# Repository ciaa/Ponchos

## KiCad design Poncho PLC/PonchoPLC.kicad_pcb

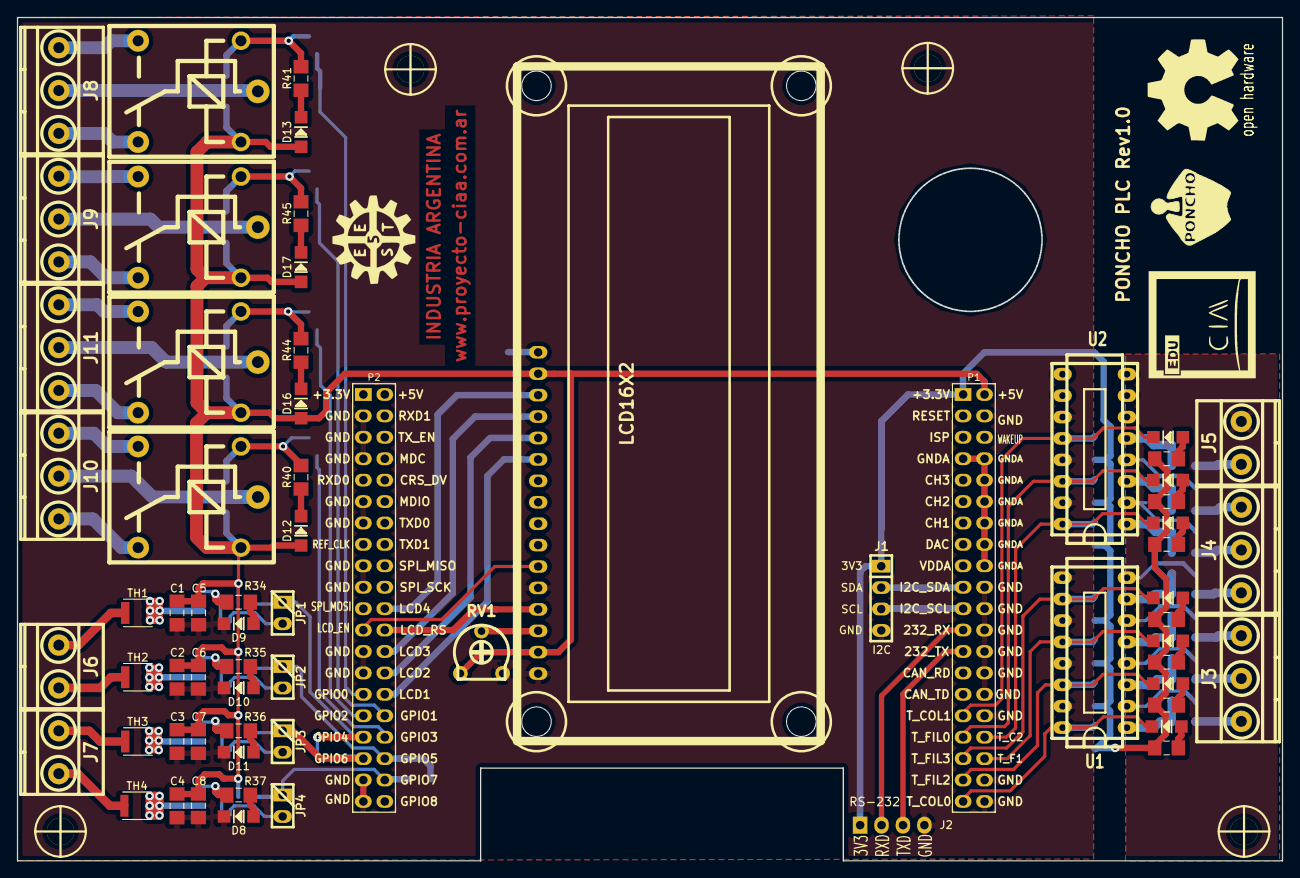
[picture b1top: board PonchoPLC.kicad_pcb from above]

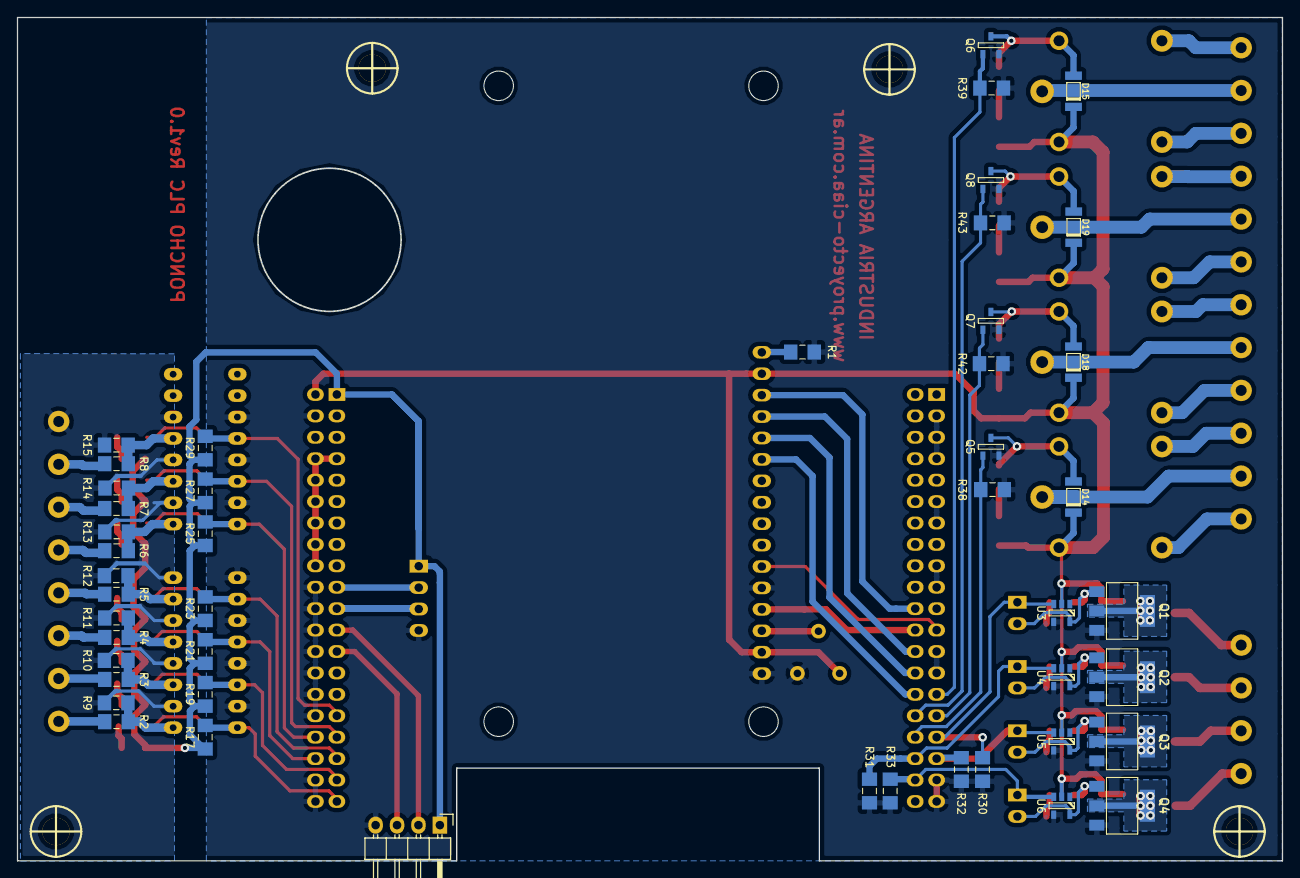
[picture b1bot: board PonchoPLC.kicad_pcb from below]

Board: 2 copper layers, 150.0 x 100.0 mm, 118 parts (47 on the bottom side), 89 nets.

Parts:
C1, C2, C3, C4: 100nF; C_1206
C5, C6, C7, C8: 1uF; C_1206
D1, D2, D3, D4, D5, D6, D7, D8, D9, D10, D11, D12, D13, D16, D17: LED red; LED_1206
D14, D15, D18, D19: LL4148; SOD80C
DS1: LCD16X2; LCD_16x2
G1: LOGO; LOGO_EESTN5
G2: LOGO; Logo_silk_OSHW_12x13mm
H1, H2, H3, H4: Mounting_Hole; Separador_M3_5mm
J1: I2C; pin_strip_4
J2: RS-232; HEADER-4H
J3, J4, J8, J9, J10, J11: TB_1X3; BORNERA3
J5, J6, J7: TB_1X2; BORNERA2
JP1, JP2, JP3, JP4: Jumper; Pin_strip_2
K1, K2, K3, K4: RELAY_C; Relay_C
Q1, Q2, Q3, Q4: FQT13N06L; SOT-223
Q5, Q6, Q7, Q8: 2N7002; SOT23
R1: 100; R_1206
R2, R3, R4, R5, R6, R7, R8: 3.3k; R_1206
R9, R10, R11, R12, R13, R14, R15: 4.7k; R_1206
R16, R18, R20, R22, R24, R26, R28: 2.2k; R_1206
R17, R19, R21, R23, R25, R27, R29, R30, R31, R32, R33, R38, R39, R42, R43: 100k; R_1206
R34, R35, R36, R37, R40, R41, R44, R45: 330; R_1206
RV1: 10K; TRIMER_V
TH1, TH2, TH3, TH4: PTS12066V100; PTC_1210
U1, U2: TLP627-4; DIP_16-300_socket
U3, U4, U5, U6: MCP1416; SOT-23-5
XA1: Conn_Poncho2P_2x_20x2; Conector_EDU_CIA_SOLO

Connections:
+3V3: J1.1, J2.1, R16.2, R17.2, R18.2, R19.2, R20.2, R21.2, R22.2, R23.2, R24.2, R25.2, R26.2, R27.2, R28.2, R29.2, XA1.1
+5V: C1.2, C2.2, C3.2, C4.2, C5.2, C6.2, C7.2, C8.2, D12.1, D13.1, D14.2, D15.2, D16.1, D17.1, D18.2, D19.2, DS1.2, DS1.15, K1.5, K2.5, K3.5, K4.5, RV1.1, U3.2, U4.2, U5.2, U6.2, XA1.2
/Conector del Poncho/COL1: D7.2, R29.1, U2.12, XA1.31
/Conector del Poncho/COL2: D5.2, R25.1, U2.16, XA1.34
/Conector del Poncho/LCD1: DS1.11, XA1.70
/Conector del Poncho/LCD2: DS1.12, XA1.68
/Conector del Poncho/LCD3: DS1.13, XA1.66
/Conector del Poncho/LCD4: DS1.14, XA1.62
/Conector del Poncho/LCD_EN: DS1.6, XA1.63
/Conector del Poncho/RS: DS1.4, XA1.64
/Conector del Poncho/RXD: J2.2, XA1.23
/Conector del Poncho/SCL: J1.3, XA1.21
/Conector del Poncho/SDA: J1.2, XA1.19
/Conector del Poncho/TXD: J2.3, XA1.25
/DIN4: D1.2, R17.1, U1.16, XA1.39
/Entradas Optoacopladas/DIN2: D6.2, R27.1, U2.14, XA1.33
/Entradas Optoacopladas/DIN3: D3.2, R21.1, U1.12, XA1.36
/Entradas Optoacopladas/DIN5: D2.2, R19.1, U1.14, XA1.37
/Entradas Optoacopladas/DIN6: D4.2, R23.1, U1.10, XA1.35
/Entradas Optoacopladas/IN0: J3.1, R2.1
/Entradas Optoacopladas/IN1: J3.2, R3.1
/Entradas Optoacopladas/IN2: J3.3, R4.1
/Entradas Optoacopladas/IN3: J4.1, R5.1
/Entradas Optoacopladas/IN4: J4.2, R6.1
/Entradas Optoacopladas/IN5: J4.3, R7.1
/Entradas Optoacopladas/IN6: J5.1, R8.1
/Salidas Digitales/C1A: J8.2, K2.1
/Salidas Digitales/C1B: J9.2, K4.1
/Salidas Digitales/C1C: J10.2, K1.1
/Salidas Digitales/C1D: J11.2, K3.1
/Salidas Digitales/DOUT0: Q6.1, R39.1, XA1.69
/Salidas Digitales/DOUT1: Q8.1, R43.1, XA1.72
/Salidas Digitales/DOUT2: Q7.1, R42.1, XA1.71
/Salidas Digitales/DOUT3: Q5.1, R38.1, XA1.74
/Salidas Digitales/DOUT4: JP1.1, R30.1, U3.3, XA1.73
/Salidas Digitales/DOUT5: JP2.1, R31.1, U4.3, XA1.76
/Salidas Digitales/DOUT6: JP3.1, R32.1, U5.3, XA1.75
/Salidas Digitales/DOUT7: JP4.1, R33.1, U6.3, XA1.78
/Salidas Digitales/NC1A: J8.3, K2.4
/Salidas Digitales/NC1B: J9.3, K4.4
/Salidas Digitales/NC1C: J10.3, K1.4
/Salidas Digitales/NC1D: J11.3, K3.4
/Salidas Digitales/NO1A: J8.1, K2.3
/Salidas Digitales/NO1B: J9.1, K4.3
/Salidas Digitales/NO1C: J10.1, K1.3
/Salidas Digitales/NO1D: J11.1, K3.3
GND: C1.1, C2.1, C3.1, C4.1, C5.1, C6.1, C7.1, C8.1, D8.2, D9.2, D10.2, D11.2, DS1.1, DS1.5, J1.4, J2.4, Q1.3, Q2.3, Q3.3, Q4.3, Q5.3, Q6.3, Q7.3, Q8.3, R1.2, R30.2, R31.2, R32.2, R33.2, R38.2, R39.2, R42.2, R43.2, RV1.3, U1.9, U1.11, U1.13, U1.15, U2.11, U2.13, U2.15, U3.4, U4.4, U5.4, U6.4, XA1.4, XA1.20, XA1.22, XA1.24, XA1.26, XA1.28, XA1.30, XA1.32, XA1.38, XA1.40, XA1.43, XA1.45, XA1.47, XA1.51, XA1.53, XA1.57, XA1.59, XA1.65, XA1.67, XA1.77, XA1.79
GNDA: XA1.7, XA1.8, XA1.10, XA1.12, XA1.14, XA1.16, XA1.18
GNDD: J5.2, R9.1, R10.1, R11.1, R12.1, R13.1, R14.1, R15.1, U1.2, U1.4, U1.6, U1.8, U2.2, U2.4, U2.6
unnamed: D1.1, R16.1
unnamed: D2.1, R18.1
unnamed: D3.1, R20.1
unnamed: D4.1, R22.1
unnamed: D5.1, R24.1
unnamed: D6.1, R26.1
unnamed: D7.1, R28.1
unnamed: D8.1, R37.1
unnamed: D9.1, R34.1
unnamed: D10.1, R35.1
unnamed: D11.1, R36.1
unnamed: D12.2, R40.2
unnamed: D13.2, R41.2
unnamed: D14.1, K1.2, Q5.2, R40.1
unnamed: D15.1, K2.2, Q6.2, R41.1
unnamed: D16.2, R44.2
unnamed: D17.2, R45.2
unnamed: D18.1, K3.2, Q7.2, R44.1
unnamed: D19.1, K4.2, Q8.2, R45.1
unnamed: DS1.3, RV1.2
unnamed: DS1.16, R1.1
unnamed: J6.1, TH1.2
unnamed: J6.2, TH2.2
unnamed: J7.1, TH3.2
unnamed: J7.2, TH4.2
unnamed: JP1.2, Q1.1, R34.2, U3.5
unnamed: JP2.2, Q2.1, R35.2, U4.5
unnamed: JP3.2, Q3.1, R36.2, U5.5
unnamed: JP4.2, Q4.1, R37.2, U6.5
unnamed: Q1.2, Q1.4, TH1.1
unnamed: Q2.2, Q2.4, TH2.1
unnamed: Q3.2, Q3.4, TH3.1
unnamed: Q4.2, Q4.4, TH4.1
unnamed: R2.2, R9.2, U1.1
unnamed: R3.2, R10.2, U1.3
unnamed: R4.2, R11.2, U1.5
unnamed: R5.2, R12.2, U1.7
unnamed: R6.2, R13.2, U2.1
unnamed: R7.2, R14.2, U2.3
unnamed: R8.2, R15.2, U2.5

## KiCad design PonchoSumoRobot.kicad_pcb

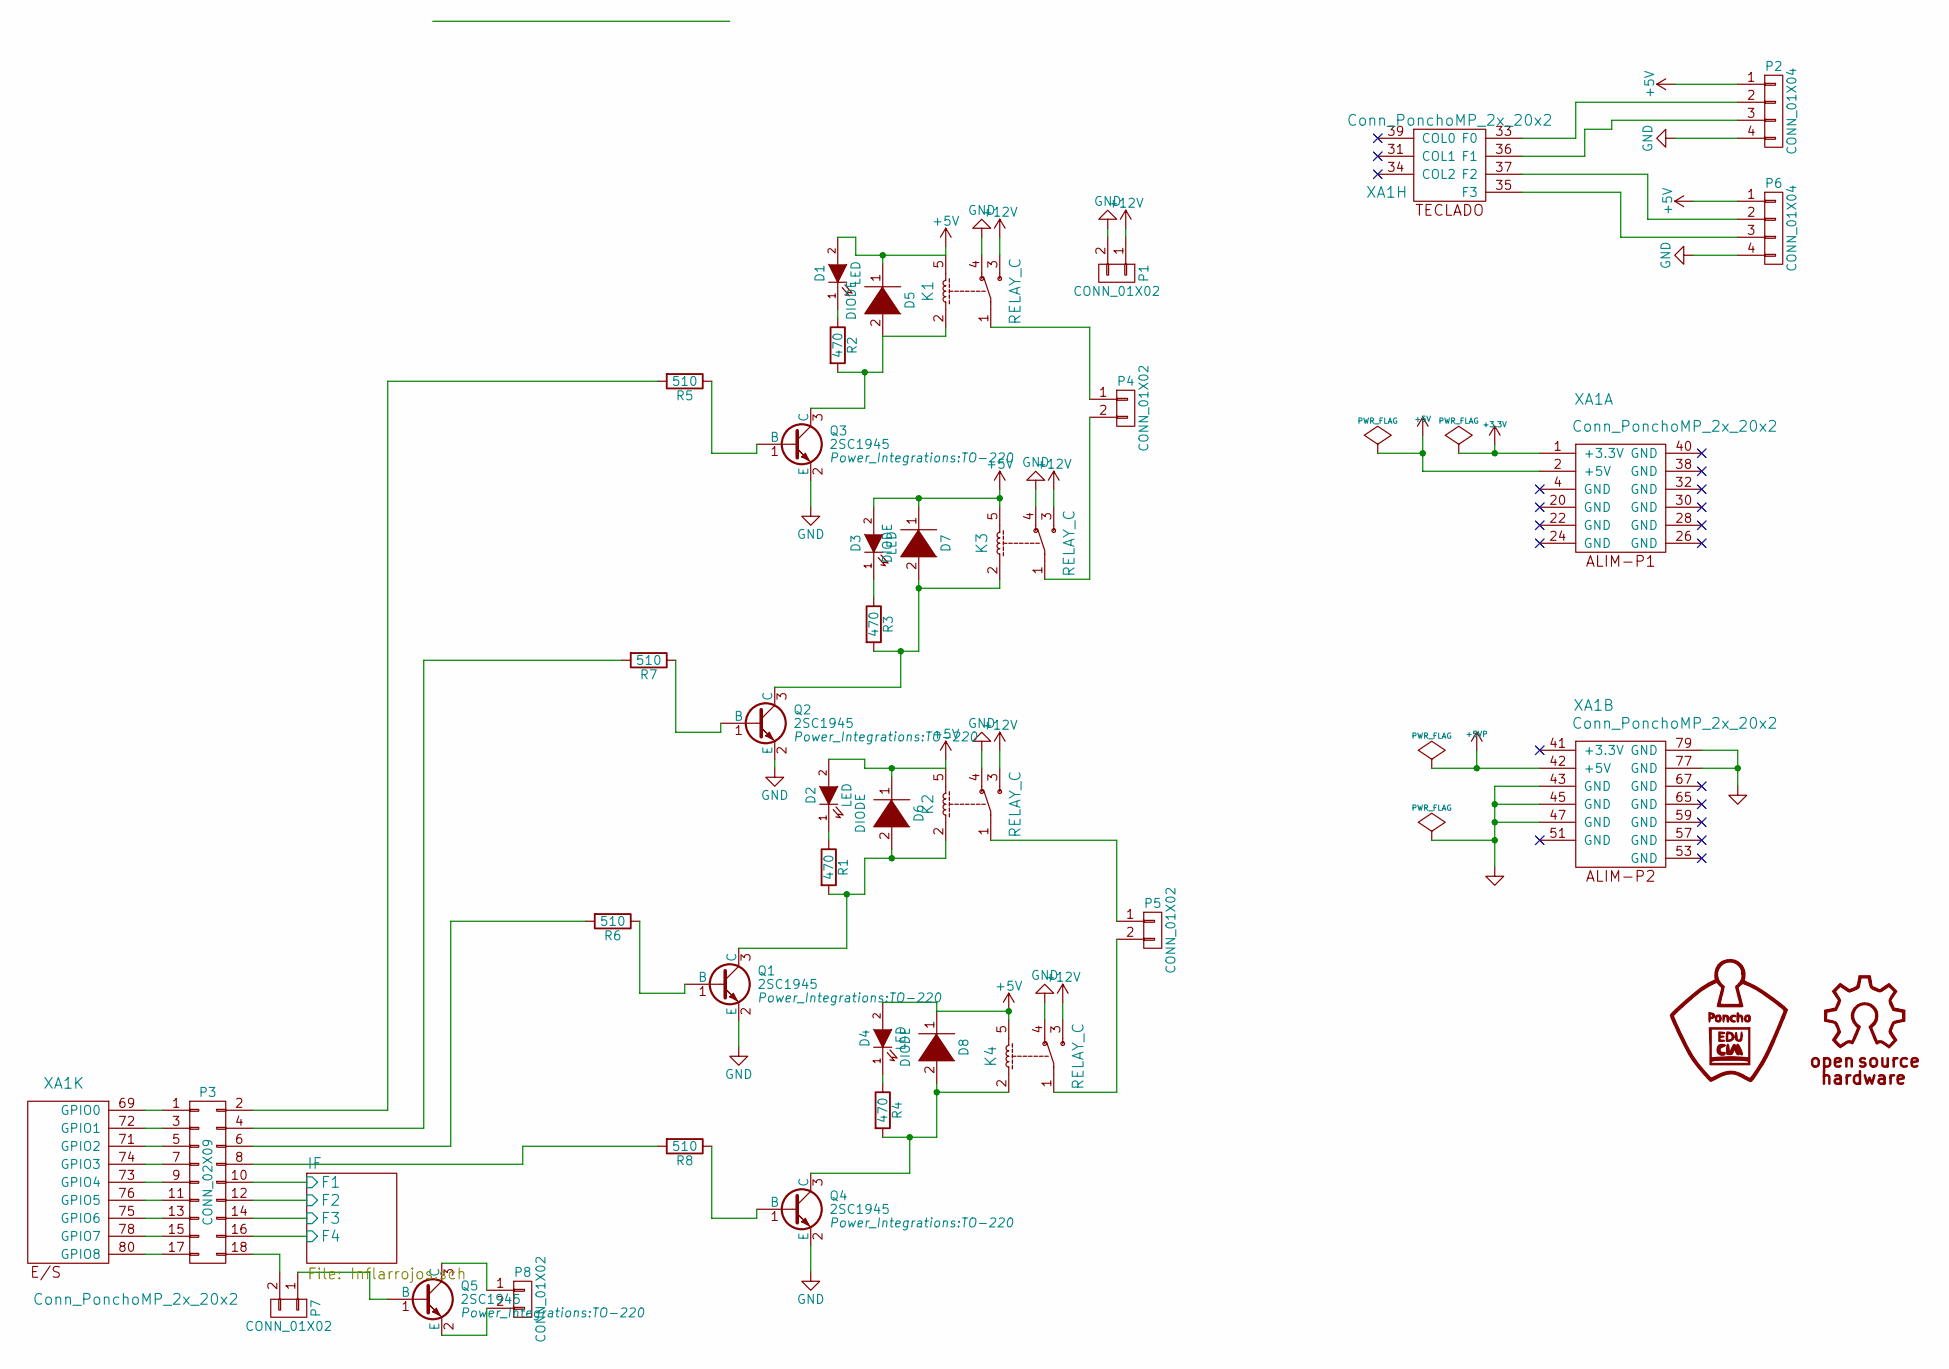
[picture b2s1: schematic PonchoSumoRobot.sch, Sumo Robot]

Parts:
D1, D2, D3, D4: LED; LED-3MM
D5, D6, D7, D8: DIODE; Diode_DO-41_SOD81_Horizontal_RM10
K1, K2, K3, K4: RELAY_C; Relay_SANYOU_SRD_Series_Form_C
P1, P4, P5: CONN_01X02; bornier2
P2, P6: CONN_01X04; Pin_Header_Straight_1x04
P3: CONN_02X09; Pin_Header_Straight_2x09
P7, P8: CONN_01X02; Pin_Header_Straight_1x02
Q1, Q2, Q3, Q4, Q5: 2SC1945; TO-220
R1, R2, R3, R4: 470; Resistor_Horizontal_RM7mm
R5, R6, R7, R8: 510; Resistor_Horizontal_RM7mm
XA1: Conn_PonchoMP_2x_20x2; Conn_Poncho_SinBorde

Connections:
+3V3: XA1.1 (+3.3V)
+5VP: XA1.42 (+5V)
+12V: K1.3, K2.3, K3.3, K4.3, P1.1
/IF/F1: P3.10; also elsewhere on the board
/IF/F2: P3.12; also elsewhere on the board
/IF/F3: P3.14; also elsewhere on the board
/IF/F4: P3.16; also elsewhere on the board
GND: K1.4, K2.4, K3.4, K4.4, P1.2, P2.4, P6.4, Q1.2 (E), Q2.2 (E), Q3.2 (E), Q4.2 (E), XA1.43 (GND), XA1.45 (GND), XA1.47 (GND), XA1.77 (GND), XA1.79 (GND); also elsewhere on the board
unnamed: D1.1 (K), R2.1
unnamed: D2.1 (K), R1.1
unnamed: D3.1 (K), R3.1
unnamed: D4.1 (K), R4.1
unnamed: D5.2 (A), K1.2, Q3.3 (C), R2.2
unnamed: D6.2 (A), K2.2, Q1.3 (C), R1.2
unnamed: D7.2 (A), K3.2, Q2.3 (C), R3.2
unnamed: D8.2 (A), K4.2, Q4.3 (C), R4.2
unnamed: K1.1, P4.1
unnamed: K2.1, P5.1
unnamed: K3.1, P4.2
unnamed: K4.1, P5.2
unnamed: P2.2, XA1.33 (F0)
unnamed: P2.3, XA1.36 (F1)
unnamed: P3.1, XA1.69 (GPIO0)
unnamed: P3.2, R5.2
unnamed: P3.3, XA1.72 (GPIO1)
unnamed: P3.4, R7.2
unnamed: P3.5, XA1.71 (GPIO2)
unnamed: P3.6, R6.2
unnamed: P3.7, XA1.74 (GPIO3)
unnamed: P3.8, R8.2
unnamed: P3.9, XA1.73 (GPIO4)
unnamed: P3.11, XA1.76 (GPIO5)
unnamed: P3.13, XA1.75 (GPIO6)
unnamed: P3.15, XA1.78 (GPIO7)
unnamed: P3.17, XA1.80 (GPIO8)
unnamed: P3.18, P7.2
unnamed: P6.2, XA1.37 (F2)
unnamed: P6.3, XA1.35 (F3)
unnamed: P7.1, Q5.1 (B)
unnamed: Q1.1 (B), R6.1
unnamed: Q2.1 (B), R7.1
unnamed: Q3.1 (B), R5.1
unnamed: Q4.1 (B), R8.1

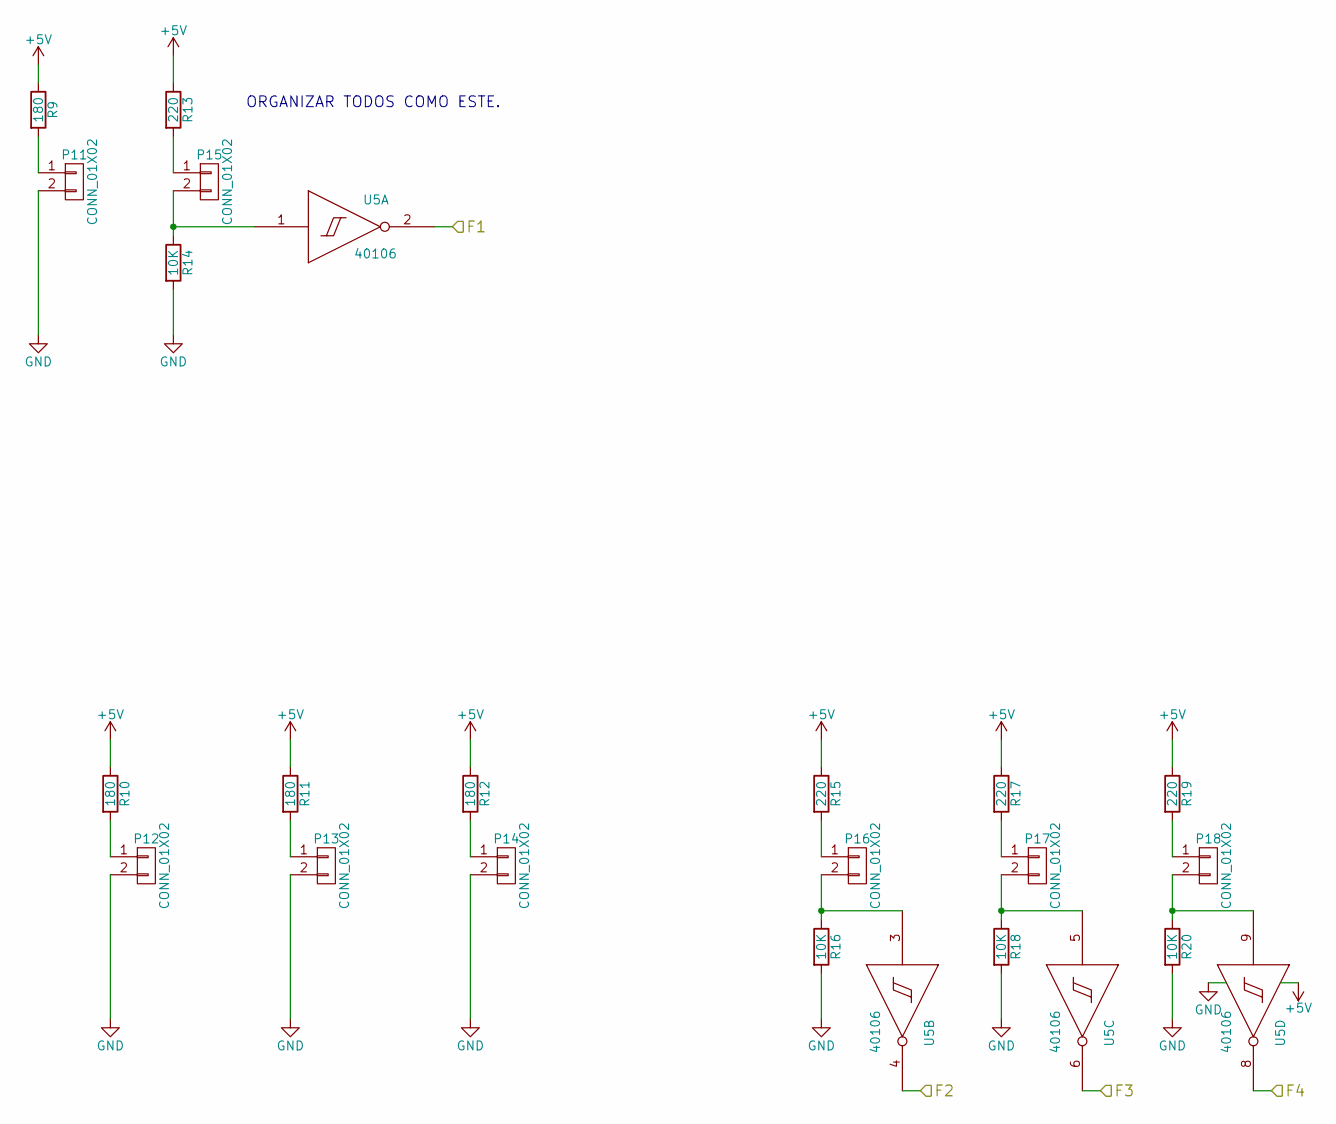
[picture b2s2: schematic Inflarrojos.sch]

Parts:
P11, P12, P13, P14, P15, P16, P17, P18: CONN_01X02; Pin_Header_Straight_1x02
R9, R10, R11, R12: 180; Resistor_Horizontal_RM7mm
R13, R15, R17, R19: 220; Resistor_Horizontal_RM7mm
R14, R16, R18, R20: 10K; Resistor_Horizontal_RM7mm
U5: 40106; 40xx-DIL14

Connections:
/IF/F1: U5.2 (Out); also elsewhere on the board
/IF/F2: U5.4 (Out); also elsewhere on the board
/IF/F3: U5.6 (Out); also elsewhere on the board
/IF/F4: U5.8 (Out); also elsewhere on the board
GND: P11.2, P12.2, P13.2, P14.2, R14.2, R16.2, R18.2, R20.2, U5.7 (VSS); also elsewhere on the board
unnamed: P11.1, R9.2
unnamed: P12.1, R10.2
unnamed: P13.1, R11.2
unnamed: P14.1, R12.2
unnamed: P15.1, R13.2
unnamed: P15.2, R14.1, U5.1 (In)
unnamed: P16.1, R15.2
unnamed: P16.2, R16.1, U5.3 (In)
unnamed: P17.1, R17.2
unnamed: P17.2, R18.1, U5.5 (In)
unnamed: P18.1, R19.2
unnamed: P18.2, R20.1, U5.9 (In)

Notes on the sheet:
ORGANIZAR TODOS COMO ESTE.

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
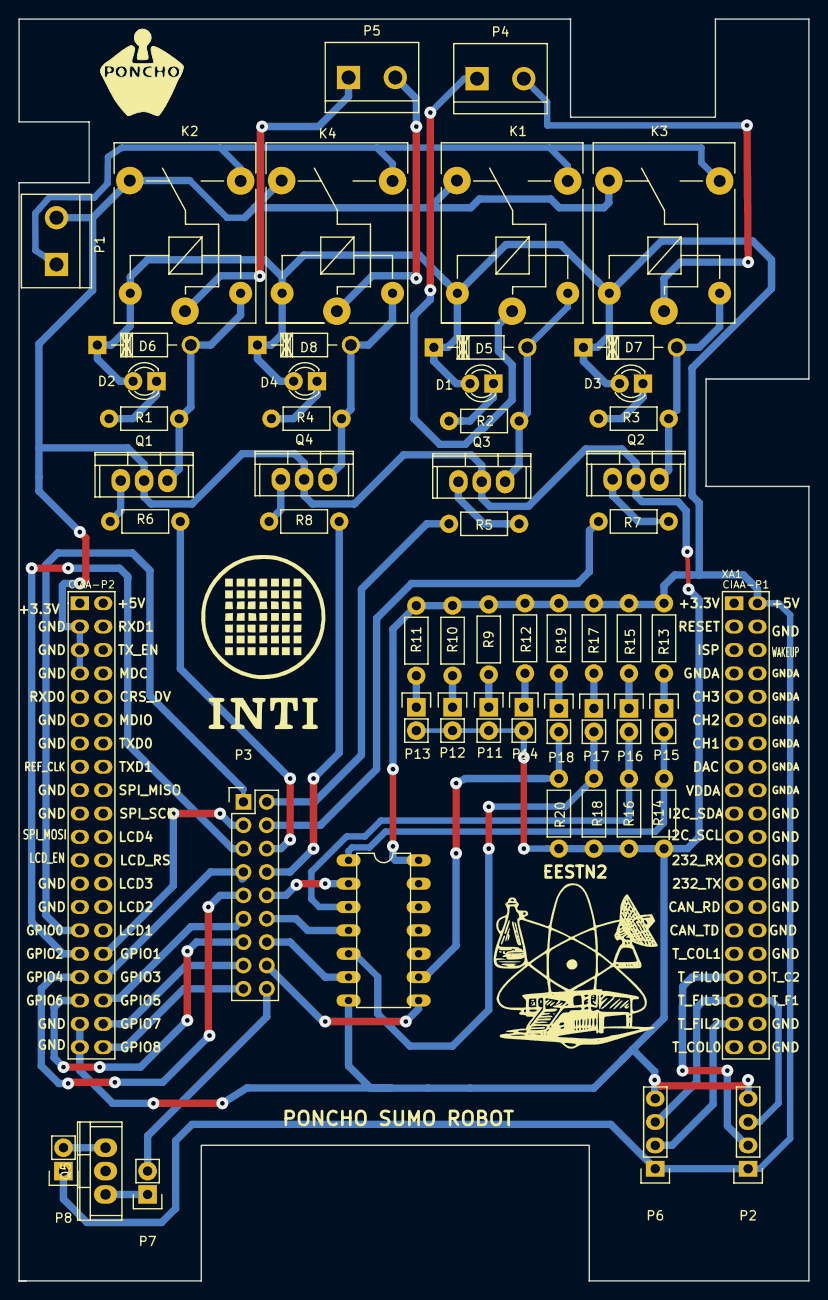
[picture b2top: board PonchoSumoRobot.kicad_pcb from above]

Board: 2 copper layers, 85.9 x 137.2 mm, 56 parts (0 on the bottom side), 55 nets.

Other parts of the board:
EESTN2: EESTN2; LOGO1

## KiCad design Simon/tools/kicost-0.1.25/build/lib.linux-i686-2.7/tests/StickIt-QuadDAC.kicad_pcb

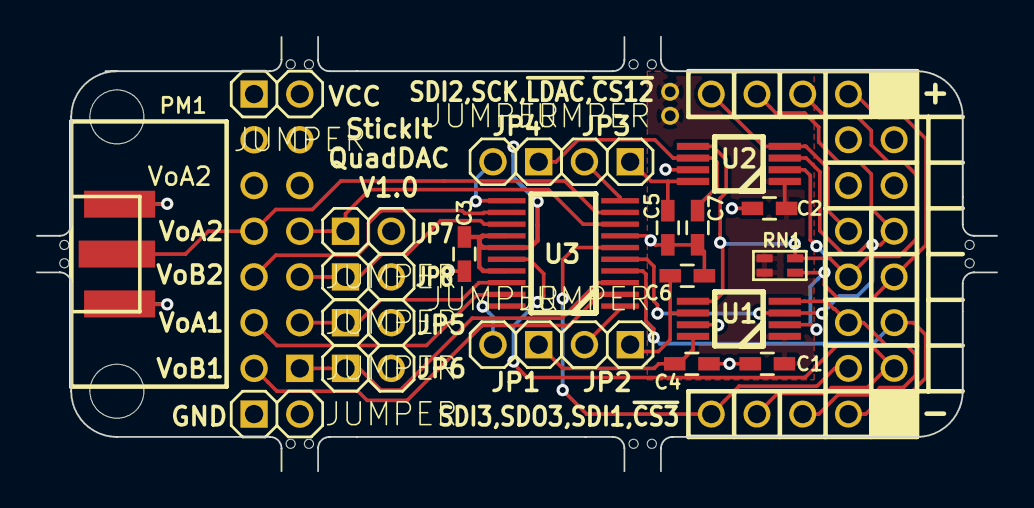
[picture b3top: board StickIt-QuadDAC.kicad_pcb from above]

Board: 2 copper layers, 53.3 x 24.1 mm, 31 parts (1 on the bottom side), 26 nets.

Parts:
A: B; oshw_logo_3mm
C1, C2, C3, C4, C5, C6, C7: C; C_0603_HandSoldering
JP1, JP2, JP3, JP4, JP5, JP6, JP7, JP8, JP9, JP10: JUMPER; HDR_1x2
PM1: PMOD_SCKT-12
RN1: 4K7; CTS_742C043
Ref**: Val**; Array_Tab_2hole
Ref**#2, Ref**#3, Ref**#4, Ref**#5, Ref**#6: Val**; Array_Tab_2hole
STK1: STICKIT2_HDR
U1, U2: MCP48X2; xess-MICROCHIP-8_MSOP
U3: MCP43X1; xess-MICROCHIP-20_TSSOP
VoA2: COAX_CONN; SMA_EDGE_AMP_132322

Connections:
/VoutA1: PM1.8, U3.19
/VoutA2: PM1.10, U3.9, VoA2.CNTR
/VoutB1: PM1.7, U3.2
/VoutB2: PM1.9, U3.12
GND: C1.2, C2.2, C3.2, C4.2, C5.2, C6.2, C7.2, JP5.2, JP6.2, JP7.2, JP8.2, JP9.1, JP9.2, PM1.5, PM1.11, STK1.GND, U1.7, U2.7, U3.7, VoA2.SHLD
unnamed: C4.1, JP1.1, U1.8
unnamed: C5.1, JP3.1, U2.8
unnamed: C6.1, JP2.1, U1.6
unnamed: C7.1, JP4.1, U2.6
unnamed: JP1.2, U3.20
unnamed: JP2.2, U3.1
unnamed: JP3.2, U3.10
unnamed: JP4.2, U3.11
unnamed: JP5.1, PM1.2, U3.18
unnamed: JP6.1, PM1.1, U3.3
unnamed: JP7.1, PM1.4, U3.8
unnamed: JP8.1, PM1.3, U3.13
SCK: STK1.D7, U1.3, U2.3, U3.5
SDI1: STK1.D2, U1.4
SDI2: STK1.D6, U2.4
SDI3: STK1.D0, U3.6
SDO3: STK1.D1, U3.16
VCC: C1.1, C2.1, C3.1, JP10.1, JP10.2, PM1.6, PM1.12, RN1.1, RN1.2, STK1.VCC, U1.1, U2.1, U3.14, U3.15, U3.17
~CS3: STK1.D3, U3.4
~CS12: RN1.3, STK1.D5, U1.2, U2.2
~LDAC: RN1.4, STK1.D4, U1.5, U2.5

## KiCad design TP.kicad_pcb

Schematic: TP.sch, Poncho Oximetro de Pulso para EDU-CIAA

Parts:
C1, C2: 10pF; C_0805; digikey# 1276-1109-1-ND
C3, C5, C6, C7: 0.01uF; C_0805; digikey# 490-8297-1-ND
C4, C9: 100nF; C_0805; digikey# 478-3351-1-ND
C8, C10: 2.2uF; C_0805; digikey# 478-2580-1-ND
C11: 1uF; C_0805; digikey# 478-1405-1-ND
J1: DB9; DB9_F_TH; digikey# AE10921-ND
R1: 1K; R_0805; digikey# 311-1.0KARCT-ND
R2: 10K; R_0805; digikey# RMCF0805JT10K0CT-ND
U1: AFE4490; QFN40; digikey# 296-35685-1-ND
XA1: Conn_Poncho2P_2x_20x2; Conn_Poncho_Izquierdo; digikey# 952-1387-ND
Y1: 8MHz; Crystal_Round_Horizontal_3mm; digikey# CTX768-ND

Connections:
+3V3: C3.1, C4.2, C5.1, C6.1, C9.1, C11.2, R2.2, U1.11, U1.17, U1.18, U1.31, U1.33, U1.39, XA1.41 (+3.3V)
GND: C1.2, C2.2, C3.2, C4.1, C5.2, C6.2, C7.2, C8.2, C9.2, C10.2, C11.1, J1.7, U1.3, U1.8, U1.12, U1.13, U1.16, U1.19, U1.32, U1.36, U1.40, U1.41, XA1.43 (GND), XA1.45 (GND), XA1.47 (GND), XA1.51 (GND), XA1.53 (GND), XA1.57 (GND), XA1.59 (GND), XA1.65 (GND), XA1.67 (GND), XA1.77 (GND), XA1.79 (GND)
unnamed: C1.1, U1.37, Y1.1
unnamed: C2.1, U1.38, Y1.2
unnamed: C7.1, R1.2
unnamed: C8.1, U1.7
unnamed: C10.1, U1.9
unnamed: J1.2, U1.15
unnamed: J1.3, U1.14
unnamed: J1.5, U1.1
unnamed: J1.9, U1.2
unnamed: R1.1, U1.4
unnamed: R2.1, U1.29, XA1.72 (GPIO1)
unnamed: U1.20, XA1.75 (GPIO6)
unnamed: U1.21, XA1.73 (GPIO4)
unnamed: U1.24, XA1.60 (spiSCK)
unnamed: U1.25, XA1.58 (spiMISO)
unnamed: U1.26, XA1.61 (spiMOSI)
unnamed: U1.27, XA1.69 (GPIO0)
unnamed: U1.28, XA1.71 (GPIO2)

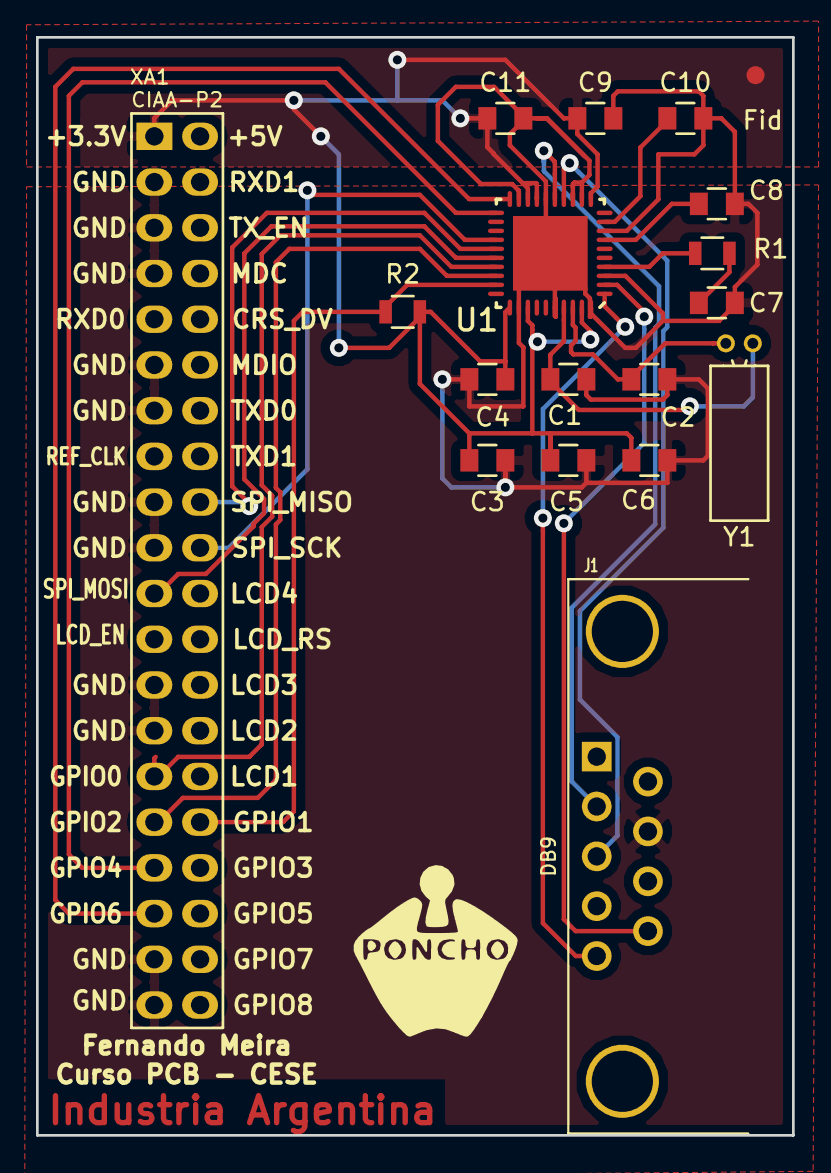
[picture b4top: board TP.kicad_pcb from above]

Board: 2 copper layers, 42.0 x 61.0 mm, 19 parts (0 on the bottom side), 20 nets.

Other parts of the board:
Fid: Fiducial_1mm_Dia_2.54mm_Outer_CopperTop
Oximentro : LOGO; Logo_Poncho

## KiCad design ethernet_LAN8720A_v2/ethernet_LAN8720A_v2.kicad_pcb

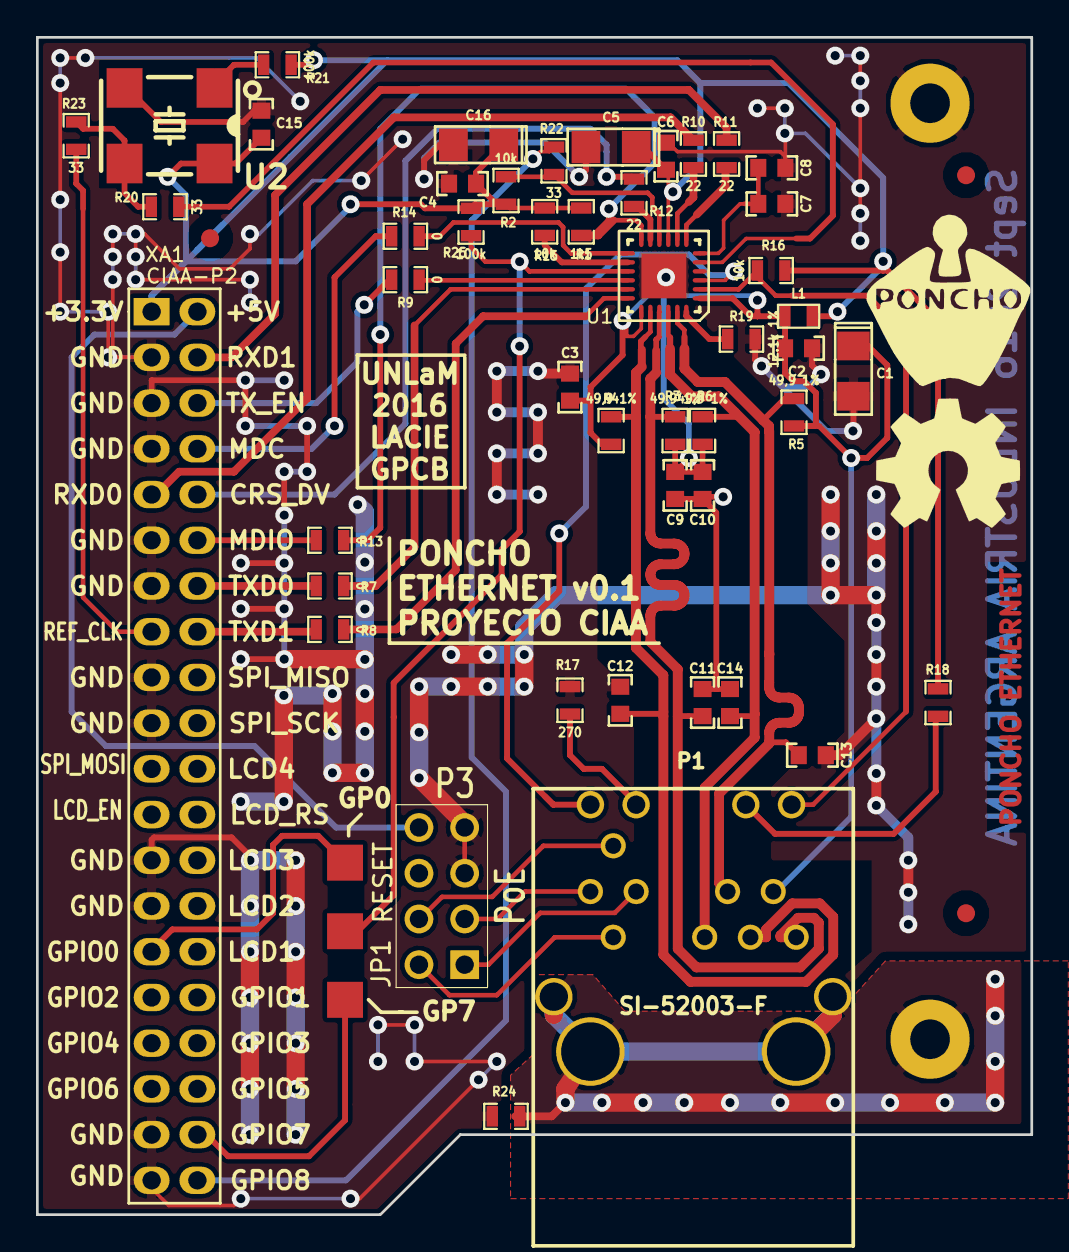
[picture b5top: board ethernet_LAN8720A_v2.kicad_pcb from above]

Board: 2 copper layers, 55.2 x 65.4 mm, 54 parts (0 on the bottom side), 45 nets.

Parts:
C1, C5, C16: 10uF; c_1206_tantalio_2
C2, C3, C6: 10nF; c_0603v2
C4, C9, C10, C15: 100nF; c_0603v2
C7: 470pF; c_0603v2
C8: 1uF; c_0603v2
C11, C12, C13, C14: 18pF; c_0603v2
FID1, FID2, FID3: FIDUCIAL; Fiducial_1mm_Dia_2.54mm_Outer_CopperTop
G101: Logo_OSHWA
JP1: JUMPER3; NetTie-II_SMD
L1: FBEAD 22; SM0603
MH1, MH2: MOUNTING-HOLE; MountingHole_2.2mm_M2_Pad
P1: SI-52003-F; RJ45_SI-52003-F_PoE_ETH
P3: PoE; PIN_ARRAY_4X2
R1: 1k5; SM0603_Resistor
R2, R15, R16: 10k; SM0603_Resistor
R3, R4, R5, R6: 49,9 1%; SM0603_Resistor
R7, R8, R9, R13, R14, R24: 0; SM0603_Resistor
R10, R11, R12: 22; SM0603_Resistor
R17, R18: 270; SM0603_Resistor
R19: 12.1k 1%; SM0603_Resistor
R20, R22, R23: 33; SM0603_Resistor
R21, R25: 100k; SM0603_Resistor
U1: LAN8720A-CP; QFN24
U2: 50MHZ; Oscillator_7.0x5.0mm
XA1: Conn_Poncho2P_2x_20x2; Conn_Poncho_Izquierdo

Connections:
+3.3V: C4.1, C5.1, C6.1, C15.1, C16.1, L1.1, R1.1, R2.1, R15.1, R16.1, R18.2, R21.2, R25.1, U1.9, U2.4, XA1.41
+5V: P3.8, XA1.42
/Circuito Principal/CHASIS: MH1.1, P1.6, P1.7, P1.16, P1.17, R24.1
/Circuito Principal/CRS: R12.1, XA1.50
/Circuito Principal/GPIO0: JP1.3, XA1.69
/Circuito Principal/GPIO7: JP1.1, XA1.78
/Circuito Principal/GPIO8: R22.1, XA1.80
/Circuito Principal/LED_100M: P1.15, R16.2, U1.2
/Circuito Principal/LED_LINK: P1.12, U1.3
/Circuito Principal/MDC: R14.1, XA1.48
/Circuito Principal/MDIO: R13.1, XA1.52
/Circuito Principal/PHY_nRESET: JP1.2, R25.2, U1.15
/Circuito Principal/RCLK: R23.2, XA1.55
/Circuito Principal/RXD0: R10.1, XA1.49
/Circuito Principal/RXD1: R11.1, XA1.44
/Circuito Principal/Rx_N: C14.1, P1.5, R6.2, U1.22
/Circuito Principal/Rx_P: C13.1, P1.4, R5.2, U1.23
/Circuito Principal/TXD0: R7.1, XA1.54
/Circuito Principal/TXD1: R8.1, XA1.56
/Circuito Principal/TXEN: R9.1, XA1.46
/Circuito Principal/Tx_N: C12.1, P1.3, R4.2, U1.20
/Circuito Principal/Tx_P: C11.1, P1.1, R3.2, U1.21
GND: C1.2, C2.2, C3.2, C4.2, C5.2, C6.2, C7.2, C8.2, C9.2, C10.2, C11.2, C12.2, C13.2, C14.2, C15.2, C16.2, MH2.1, P3.5, P3.7, R17.1, R19.2, R24.2, U1.GND, U2.2, XA1.43, XA1.45, XA1.47, XA1.51, XA1.53, XA1.57, XA1.59, XA1.65, XA1.67, XA1.77, XA1.79
unnamed: C1.1, C2.1, C3.1, C9.1, C10.1, L1.2, P1.2, R3.1, R4.1, R5.1, R6.1, U1.1, U1.19
unnamed: C7.1, C8.1, U1.6
unnamed: P1.8, P3.1
unnamed: P1.9, P3.2
unnamed: P1.10, P3.3
unnamed: P1.11, P3.4
unnamed: P1.13, R17.2
unnamed: P1.14, R18.1
unnamed: R1.2, R13.2, U1.12
unnamed: R2.2, R22.2, U1.10
unnamed: R7.2, U1.17
unnamed: R8.2, U1.18
unnamed: R9.2, U1.16
unnamed: R10.2, U1.8
unnamed: R11.2, U1.7
unnamed: R12.2, U1.11
unnamed: R14.2, U1.13
unnamed: R15.2, U1.14
unnamed: R19.1, U1.24
unnamed: R20.1, R23.1, U2.3
unnamed: R20.2, U1.5
unnamed: R21.1, U2.1

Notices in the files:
Simon/tools/kicost-0.1.25/build/lib.linux-i686-2.7/tests/StickIt-QuadDAC.kicad_pcb:
(c) 2016
CC BY 4.0
